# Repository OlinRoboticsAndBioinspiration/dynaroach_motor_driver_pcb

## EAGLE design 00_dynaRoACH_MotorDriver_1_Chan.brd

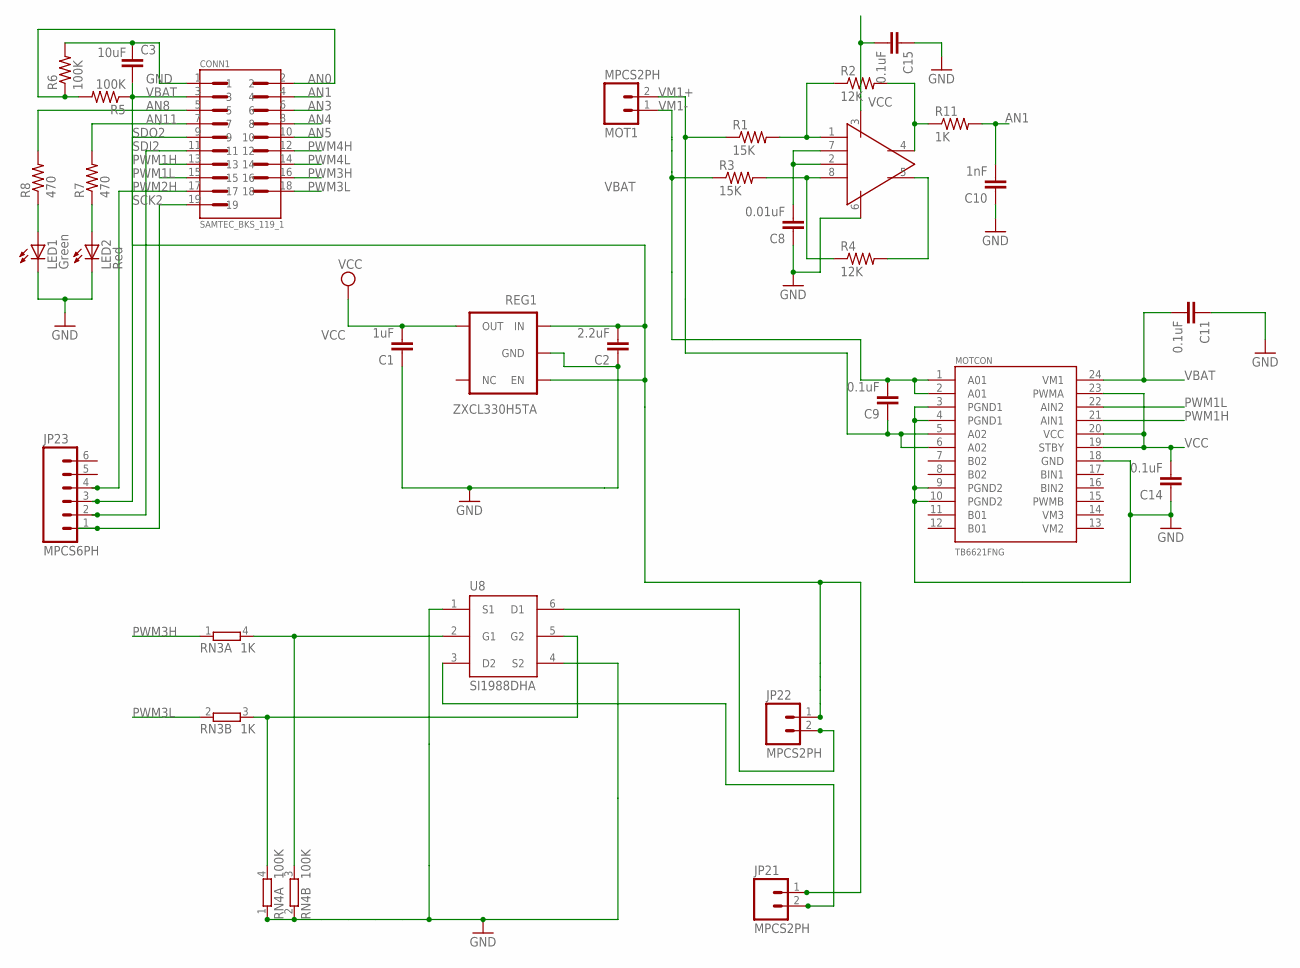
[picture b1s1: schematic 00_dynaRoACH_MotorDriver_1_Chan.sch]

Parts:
C1: 1uF; 0402-CAP
C2: 2.2uF; 0402-CAP
C3: 10uF; 0603-CAP
C8: 0.01uF; 0402-CAP
C9, C11, C14, C15: 0.1uF; 0402-CAP
C10: 1nF; 0402-CAP
CONN1: SAMTEC_BKS_119_1; SAMTEC_19P_1MM_SOCKET
JP21, JP22: MPCS2PH; MOLEX-PICO_CLASP_S2P
JP23: MPCS6PH; MOLEX-PICO_CLASP_S6P
LED1: Green; LED-0603
LED2: Red; LED-0603
MOT1: MPCS2PH; MOLEX-PICO_CLASP_S2P
MOTCON: TB6621FNG; SSOP24
R1, R3: 15K; 0402-RES
R2, R4: 12K; 0402-RES
R5, R6: 100K; 0402-RES
R7, R8: 470; 0402-RES
R11: 1K; 0402-RES
REG1: ZXCL330H5TA; SC-70-5
RN3: 1K; EXB24V
RN4: 100K; EXB24V
U8: SI1988DHA; SC-70-6
U$1: LTC1992; 8-PIN_MSOP

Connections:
AN0: CONN1.2, R5.2, R6.1
AN1: C10.2, CONN1.4, R11.2
AN3: CONN1.6
AN4: CONN1.8
AN5: CONN1.10
AN8: CONN1.5, R8.2
AN11: CONN1.7, R7.2
GND: C1.1, C2.1, C3.1, C8.1, C10.1, C11.1, C14.1, C15.1, CONN1.1, LED1.C, LED2.C, MOTCON.3 (PGND1), MOTCON.4 (PGND1), MOTCON.9 (PGND2), MOTCON.10 (PGND2), MOTCON.18 (GND), R6.2, REG1.2 (GND), RN4.1, RN4.2 (1), U8.1 (S1), U8.4 (S2), U$1.6 (GND)
unnamed: R1.2, R2.1, U$1.1 (-)
unnamed: R3.2, R4.1, U$1.8 (+)
unnamed: RN3.4 (2), RN4.3 (2), U8.2 (G1)
unnamed: LED1.A, R8.1
unnamed: LED2.A, R7.1
unnamed: R4.2, U$1.5 (OUT-)
unnamed: C8.2, U$1.2 (V_OCM), U$1.7 (V_MID)
unnamed: R2.2, R11.1, U$1.4 (OUT+)
unnamed: JP22.2, U8.6 (D1)
unnamed: JP21.2, U8.3 (D2)
unnamed: RN3.3 (2), RN4.4 (2), U8.5 (G2)
PWM1H: CONN1.13, MOTCON.21 (AIN1)
PWM1L: CONN1.15, MOTCON.22 (AIN2)
PWM2H: CONN1.17, JP23.4
PWM3H: CONN1.16, RN3.1
PWM3L: CONN1.18, RN3.2 (1)
PWM4H: CONN1.12
PWM4L: CONN1.14
SCK2: CONN1.19, JP23.1
SDI2: CONN1.11, JP23.2
SDO2: CONN1.9, JP23.3
VBAT: C2.2, C3.2, C11.2, CONN1.3, JP21.1, JP22.1, MOTCON.24 (VM1), R5.1, REG1.1 (IN), REG1.3 (EN)
VCC: C1.2, C14.2, C15.2, MOTCON.19 (STBY), MOTCON.20 (VCC), MOTCON.23 (PWMA), REG1.5 (OUT), U$1.3 (VDD)
VM1+: C9.1, MOT1.2, MOTCON.5 (A02), MOTCON.6 (A02), R1.1
VM1-: C9.2, MOT1.1, MOTCON.1 (A01), MOTCON.2 (A01), R3.1

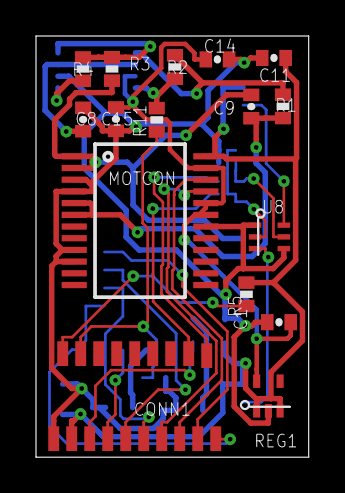
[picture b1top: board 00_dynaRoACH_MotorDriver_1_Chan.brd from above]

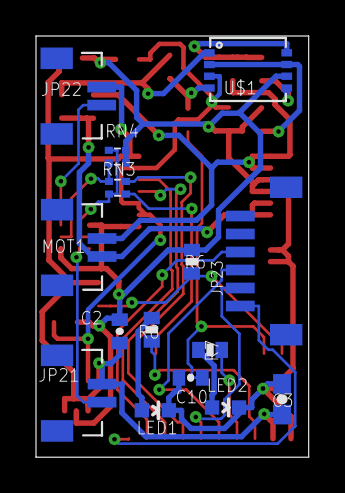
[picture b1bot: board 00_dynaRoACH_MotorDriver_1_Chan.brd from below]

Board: 2 copper layers, 15.1 x 23.4 mm, 31 parts (15 on the bottom side), 28 nets.

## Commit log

2014-10-23 Added dsn and scr files for interfacing with freerouter
2014-10-23 Updated board layout to add SPI 6 pin breakout
2014-10-26 updated some silkscreen labels
2014-10-29 Updates to motor driver brd
